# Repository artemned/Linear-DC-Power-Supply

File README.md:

# Linear-DC-Power-Supply
##  Board source dc voltage and dc current.   

## One of the possible types power supplies

### I was inspired to create this project by the advice of my colleagues and the lack of a regulated DC voltage and DC power supply. I also wanted to practice PCB design. I used Eagle CAD for this. The project is based on one of the schematics in The Art of Circuitry by Paul Horowitz and Hill Winfield. There are many variants of this device on the network, but it seems to me that it is simpler and does not require many components. Of course, this scheme has a number of positive changes compared to the original. Everything you need to make a board and assemble a device is in the repository.I am sure that even a novice radio amateur will be able to assemble it, and if something suddenly does not work out, then write to the email address: daineko.a32@mail.ru.    P.S. All goodness and fresh cookies!

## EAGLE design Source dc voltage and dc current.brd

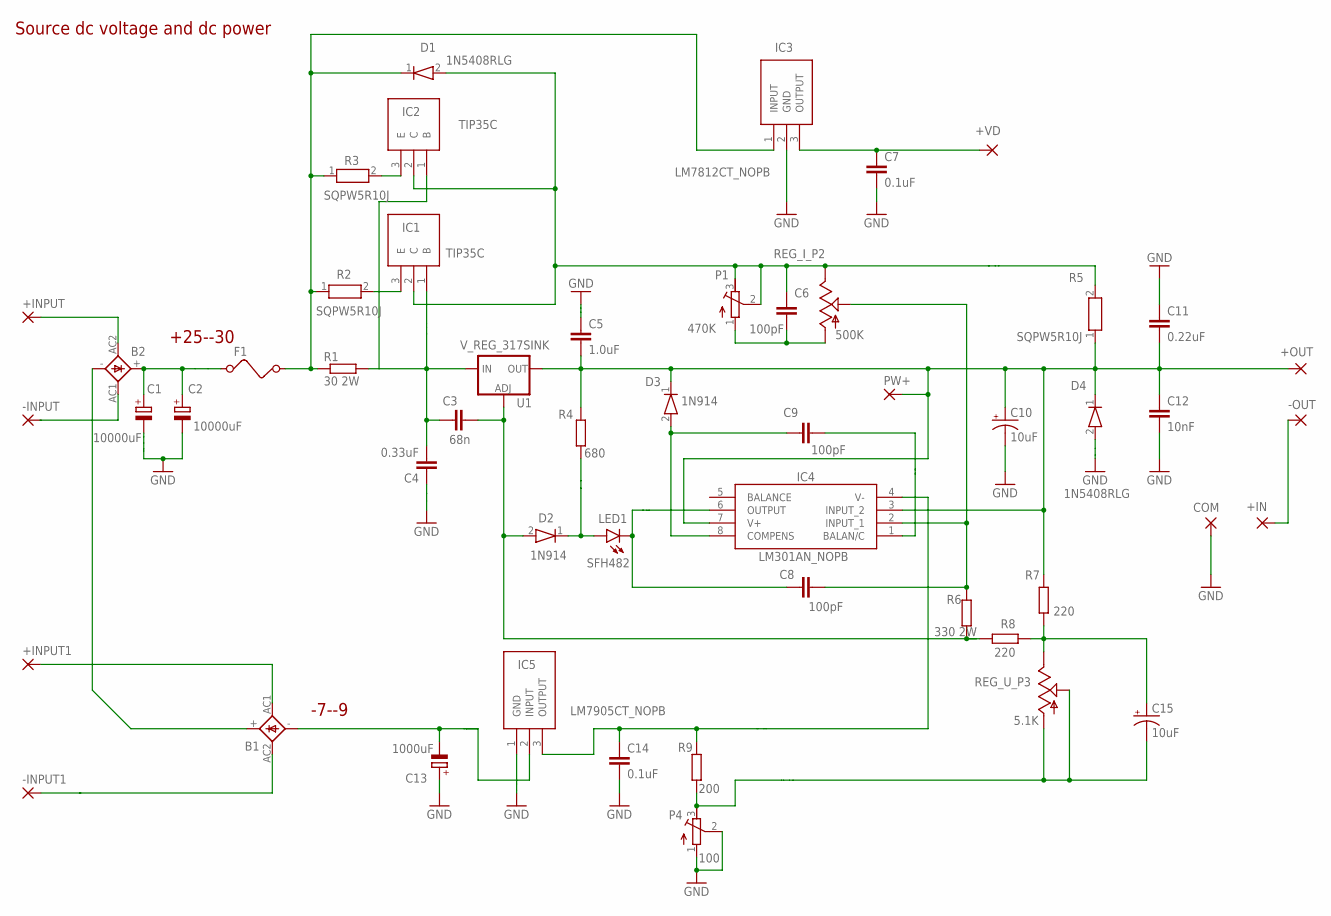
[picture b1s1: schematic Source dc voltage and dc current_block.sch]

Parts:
+IN: 3,17/1,3
+INPUT, +INPUT1: 3,17/1,3
+OUT: 3,17/1,3
+VD: 3,81/1,4
-INPUT, -INPUT1: 3,17/1,3
-OUT: 3,17/1,3
B1, B2: FBU4
C1, C2: 10000uF; EB30D
C3: 68n; C050-025X075
C4: 0.33uF; C5B2.5
C5: 1.0uF; C050-025X075
C6, C8, C9: 100pF; C5B2.5
C7, C14: 0.1uF; C5B2.5
C10, C15: 10uF; CPOL-RADIAL-2.5MM-5MM
C11: 0.22uF; C5B2.5
C12: 10nF; C5B2.5
C13: 1000uF; EB22,5D
COM: 3,17/1,3
D1, D4: 1N5408RLG; DIOAD2860W130L840D505
D2, D3: 1N914; DIOAD1068W53L380D172
F1: FUSE
IC1, IC2: TIP35C; TO545P515X1560X2445-3P
IC3: LM7812CT_NOPB; TO254P470X1028X1955-3P
IC4: LM301AN_NOPB; DIP794W53P254L959H508Q8N
IC5: LM7905CT_NOPB; TO254P470X1028X1955-3P
LED1: SFH482
P1: 470K; RTRIM3296W
P4: 100; RTRIM3296W
PW+: 3,17/1,3
R1: 30 2W; 0207/10
R2, R3, R5: SQPW5R10J; RESAD6200W85L2200D1000
R4: 680; R1206
R6: 330 2W; 0207/10
R7, R8: 220; M1206
R9: 200; M1206
REG_I_P2: 500K; POT_ALPHA_RV16AF-20
REG_U_P3: 5.1K; POT_ALPHA_RV16AF-20
U1: V_REG_317SINK; TO220-ADJ

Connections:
12V: D1.1 (K), F1.2, IC3.1 (INPUT), R1.1, R2.1, R3.1
GND: C1.-, C2.-, C4.1, C5.1, C7.2, C10.2 (-), C11.1, C12.2, C13.+, C14.2, COM.1, D4.2 (A), IC3.2 (GND), IC5.1 (GND), P4.1 (A), P4.2 (S)
IN+: +OUT.1, C5.2, C10.1 (+), C11.2, C12.1, D3.1 (K), D4.1 (K), IC4.3 (INPUT_2), IC4.7 (V+), PW+.1, R4.2, R5.1, R7.2, U1.OUT
IN-: C6.1, D1.2 (A), IC1.2 (C), IC2.2 (C), P1.2 (S), P1.3 (E), R5.2, REG_I_P2.3 (E)
unnamed: B2.+, C1.+, C2.+, F1.1
unnamed: +VD.1, C7.1, IC3.3 (OUTPUT)
unnamed: B1.-, C13.-, IC5.2 (INPUT)
unnamed: +IN.1, -OUT.1
unnamed: D2.1 (K), LED1.A, R4.1
unnamed: IC1.3 (E), R2.2
unnamed: -INPUT.1, B2.AC1 (AC2)
unnamed: IC2.3 (E), R3.2
unnamed: C6.2, P1.1 (A), REG_I_P2.1 (A)
unnamed: +INPUT.1, B2.AC2 (AC1)
unnamed: -INPUT1.1, B1.AC2 (AC1)
unnamed: +INPUT1.1, B1.AC1 (AC2)
unnamed: C15.1 (+), R7.1, R8.1, REG_U_P3.3 (E)
unnamed: C3.1, C4.2, IC1.1 (B), IC2.1 (B), R1.2, U1.IN
unnamed: C8.1, IC4.6 (OUTPUT), LED1.K (C)
unnamed: B1.+, B2.-
unnamed: C15.2 (-), P4.3 (E), R9.1, REG_U_P3.1 (A), REG_U_P3.2 (S)
unnamed: C9.1, D3.2 (A), IC4.8 (COMPENS)
unnamed: C9.2, IC4.1 (BALAN/C)
unnamed: C8.2, IC4.2 (INPUT_1), R6.2, REG_I_P2.2 (S)
OUT: C3.2, D2.2 (A), R6.1, R8.2, U1.ADJ
VE: C14.1, IC4.4 (V-), IC5.3 (OUTPUT), R9.2

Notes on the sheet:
+25--30
-7--9
Source dc voltage and dc power

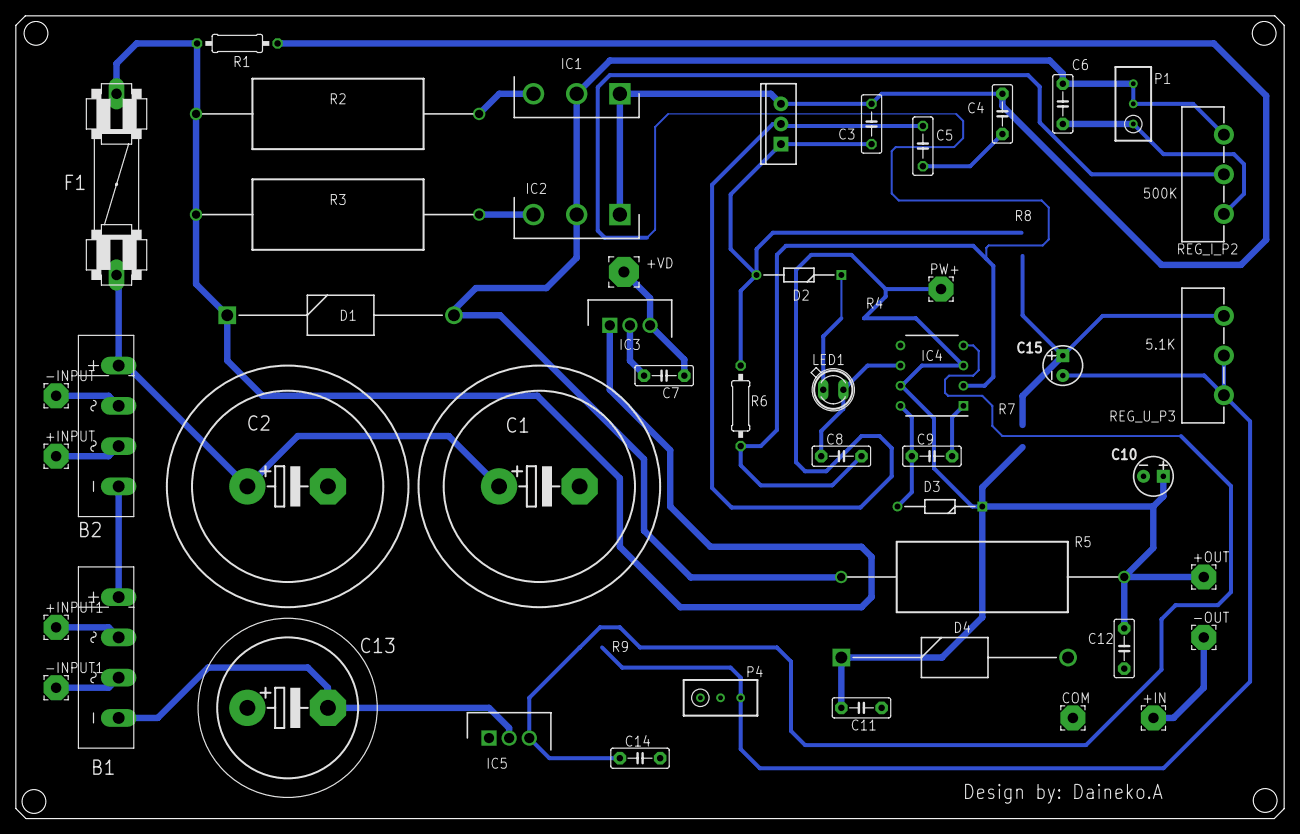
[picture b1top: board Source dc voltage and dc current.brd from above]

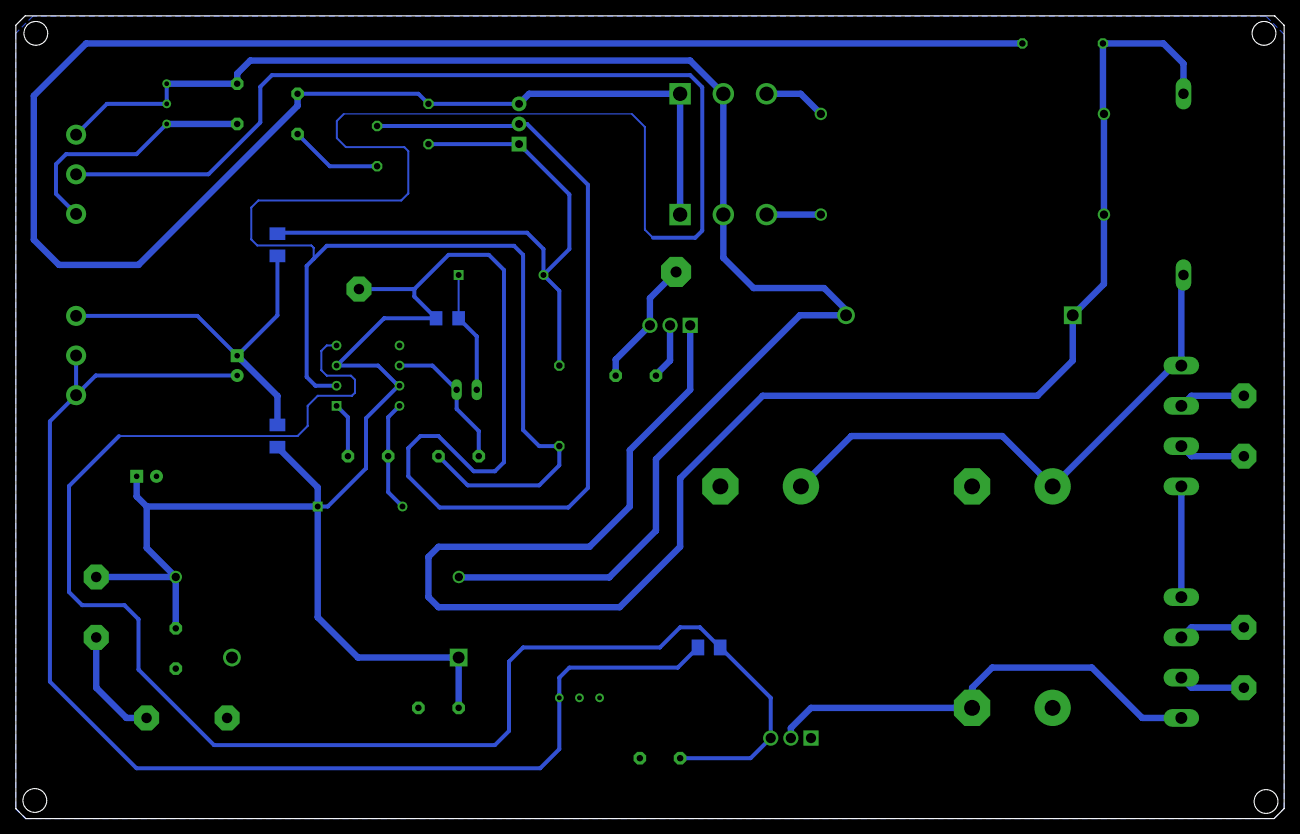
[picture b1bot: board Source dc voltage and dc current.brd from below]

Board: 2 copper layers, 160.0 x 101.3 mm, 52 parts (4 on the bottom side), 26 nets.

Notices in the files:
parts and their libraries:
SparkFun-Capacitors: Licensing: Creative Commons ShareAlike 4.0 International - https://creativecommons.org/licenses/by-sa/4.0
